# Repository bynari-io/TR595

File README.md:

# TR-595 Tricorder Project

This project is my attempt to build a customized version of the Voyager Mk IX/X Tricorder. The project will consist of a 3D printed housing and will utilize an LCD display and custom electronics driven by a Raspberry Pi Pico. All designs and code will be freely available in this repository. For more information, see the developmnent thread on the RPF: https://www.therpf.com/forums/threads/tr-595e-custom-tricorder.342650/

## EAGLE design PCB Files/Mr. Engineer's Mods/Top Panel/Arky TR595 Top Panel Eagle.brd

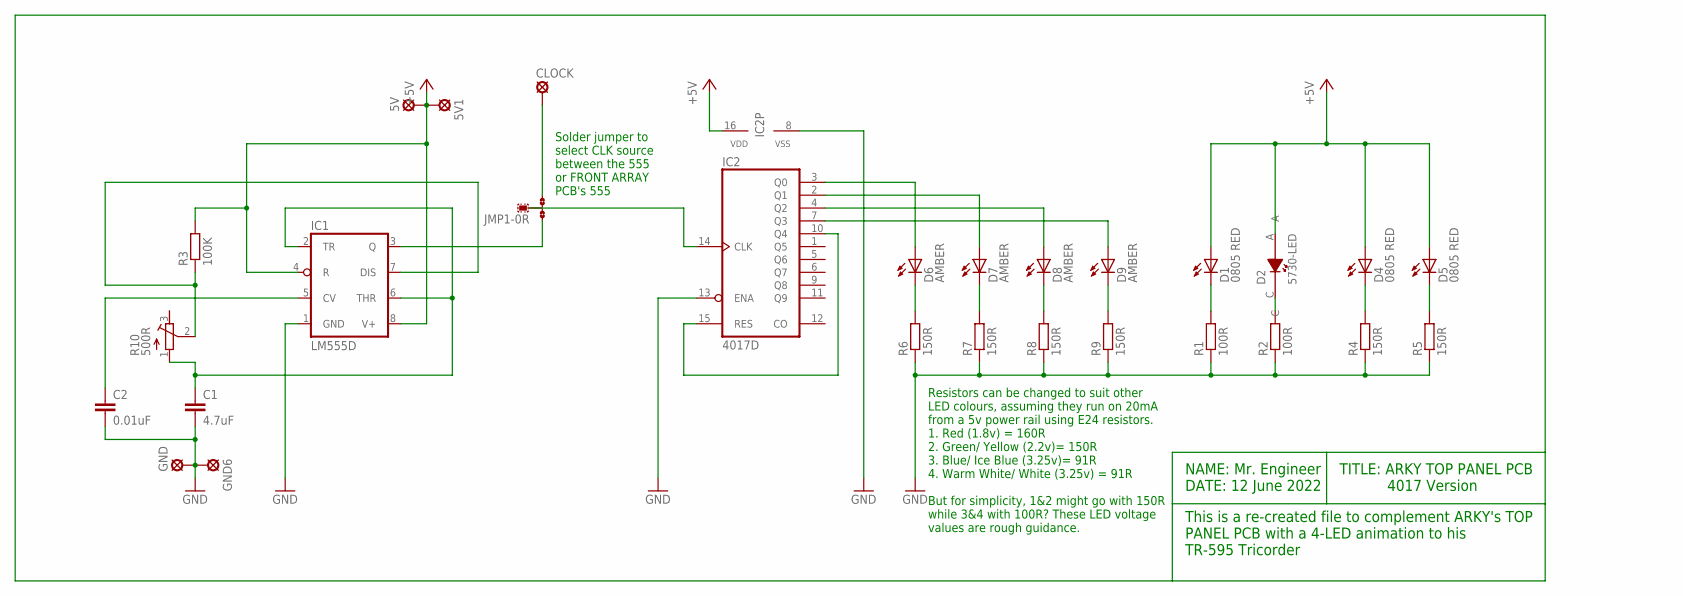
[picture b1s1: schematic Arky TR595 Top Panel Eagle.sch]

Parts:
5V, 5V1: MCS10B
C1: 4.7uF; C0805
C2: 0.01uF; C0805
CLOCK: MCS10B
D1, D4, D5: 0805 RED; CHIPLED_0805
D2: 5730-LED
D6, D7, D8, D9: AMBER; CHIPLED_0805
GND, GND6: MCS10B
IC1: LM555D; SO08
IC2: 4017D; SO16
JMP1: 0R-JUMPA; A0R-JMP
R1, R2: 100R; R0805
R3: 100K; R0805
R4, R5, R6, R7, R8, R9: 150R; R0805
R10: 500R; RTRIM3103

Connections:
+5V: 5V.MP, 5V1.MP, D1.A, D2.A, D4.A, D5.A, IC1.4 (R), IC1.8 (V+), IC2.16 (VDD), R3.2
GND: IC2.8 (VSS)
unnamed: IC1.3 (Q), JMP1.1
unnamed: C2.1, IC1.5 (CV)
unnamed: D6.C, R6.2
unnamed: D7.C, R7.2
unnamed: D8.C, R8.2
unnamed: D9.C, R9.2
unnamed: C1.1, IC1.2 (TR), IC1.6 (THR), R10.1 (A)
unnamed: D6.A, IC2.3 (Q0)
unnamed: D7.A, IC2.2 (Q1)
unnamed: D8.A, IC2.4 (Q2)
unnamed: D9.A, IC2.7 (Q3)
unnamed: IC2.10 (Q4), IC2.15 (RES)
unnamed: D4.C, R4.2
unnamed: D5.C, R5.2
unnamed: D1.C, R1.2
unnamed: D2.C, R2.2
unnamed: IC1.7 (DIS), R3.1, R10.2 (S)
unnamed: IC2.14 (CLK), JMP1.2
unnamed: CLOCK.MP, JMP1.3
unnamed: C1.2, C2.2, GND.MP, GND6.MP, IC1.1 (GND), IC2.13 (ENA), R1.1, R2.1, R4.1, R5.1, R6.1, R7.1, R8.1, R9.1

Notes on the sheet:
This is a re-created file to complement ARKY's TOP PANEL PCB with a 4-LED animation to his TR-595 Tricorder
NAME: Mr. Engineer DATE: 12 June 2022
TITLE: ARKY TOP PANEL PCB 4017 Version
Solder jumper to select CLK source between the 555 or FRONT ARRAY PCB's 555
Resistors can be changed to suit other LED colours, assuming they run on 20mA from a 5v power rail using E24 resistors. 1. Red (1.8v) = 160R 2. Green/ Yellow (2.2v)= 150R 3. Blue/ Ice Blue (3.25v)= 91R 4. Warm White/ White (3.25v) = 91R But for simplicity, 1&2 might go with 150R while 3&4 with 100R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

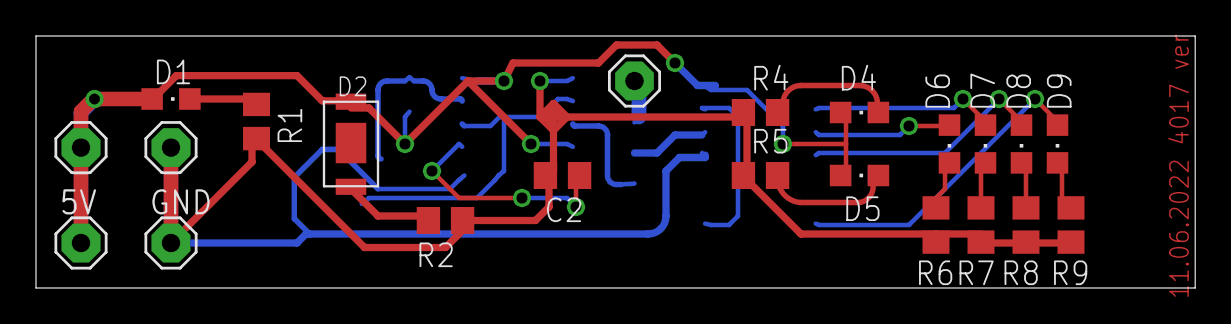
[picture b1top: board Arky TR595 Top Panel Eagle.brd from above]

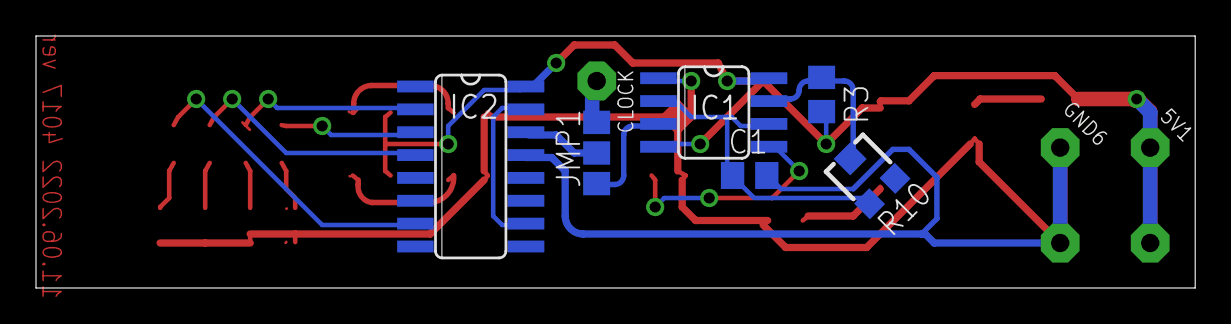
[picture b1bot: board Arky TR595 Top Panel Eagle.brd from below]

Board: 2 copper layers, 64.4 x 14.0 mm, 28 parts (6 on the bottom side), 21 nets.

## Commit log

2022-01-07 Added Project Resources folder
2022-01-07 Added main project files & boilerplate code
2022-01-07 Added info to readme
2022-01-10 Removed bargraph header from lcars.svg. Updated lcars.h to match
2022-01-11 Initial work on animation
2022-01-14 Added Anim class to hold data on animation elements
2022-01-14 Renamed lcars to defaultMode for futureproofing
2022-01-14 Wrote basic animation code. Organized code to better allow for future animations
2022-01-14 Renamed lcars.h to defaultmode.h to reflect new scanning mode name
2022-01-16 Added new background for Default Mode
2022-01-16 Added helper function GetTime()
2022-01-16 Replaced animations for old screen. Added Top/Bottom frame animation
2022-01-16 Added new .svg for Default Screen
2022-01-16 Added 'visible' attribute to class Anim
2022-01-16 Removed 'visible' attribute, added 'blinkDelay' to class Anim
2022-01-17 Added button animation to bottom-right corner
2022-01-18 Added bool sequenceComplete attribute to class Anim
2022-01-18 started work on bargraph animation
2022-01-20 Added bargraph animation
2022-01-20 Tweaks to defaultmode background & bargraph animation
2022-01-21 Added scrolling text animation
2022-01-22 Added sound effect files to resource folder
2022-02-28 Added gerber files for PCB manufacture
2022-04-17 Added decals
2022-04-17 Added Fusion 360 and STL exports
2022-04-17 Added parts list
2022-04-17 Moved arduino files to their own folder
2022-04-17 Added hinge info to parts list
2022-04-17 Updated parts list
2022-06-23 added optional door w/ ID cutout
2022-08-18 Added Mr. Engineer's Top Panel mod to PCB Files/Mr.Engineer's Mods
2023-01-28 Formatted and Corrected BOM
    Each board was split into its own sheet and all parts were given correct links
